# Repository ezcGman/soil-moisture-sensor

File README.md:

# Soil Moisture Sensor
This is one of my first self designed PCBs in KiCad. It's a simple circuit which makes use of an ESP8266 and a soil moisture sensor to observe your plants. The cool thing: My custom socket supports the ESP-12E/F, the ESP-8 and the cool ESP-7, which comes with an external antennna!

## Credits
Shoutout to Quindor from QuinLED.info, the LED master himself. He tought me a lot about KiCad, PCB design and some more electrical engineering fundamentals! While I'm still miles away from being perfect, with his help I really feel confident in what I'm doing here!

## KiCad dependencies
It might happen that KiCad is missing my custom footprints. You can find and download them here and then add them to KiCad: https://github.com/ezcGman/andys-footprints

## Parts list
All these parts can be easily found on AliExpress (except the PCBs ;) ):

- 1x The PCB in this folder, printed e.g. at PCBWay
- 1x 3.2V LiFePO4 battery in AA form factor
- 1x AA battery holder for THT mounting
- 1x capactive soil moisture sensor (some notes on capacitive vs. resistive sensors can be found a bit further down)
- 1x bare ESP8266 module, so no devboard like the famous NodeMCU or D1 Mini. The socket supports the ESP-12E/F, ESP-8 and ESP-7. But in the end, there are only two choices:
  - ESP-12E/F: If you don't need an external antenna / your Wi-Fi signal is good, get this one. It's super common, easy to get and cheap.
  - ESP-7: If you do need an external antenna, get this one. Often also comes directly with an antenna! 
- 1x NPN transistor. Probably most transistors are fine, but I suggest the 2n2222(a) which is super common and totally sufficient for this
- 1x 0805 SMD capacitor of 10µF or bigger. But 0805 SMD caps are usually limited to ~40µF. So whatever u have around
- 1x 0805 SMD capacitor of 100nF
- 1x 0805 resistor of 1kΩ
- 2x 0805 resistor of 10kΩ
- 1x 0805 resistor of 100kΩ
- 1x 0805 resistor of 220kΩ
- 2x **2mm** (**not** 2.54mm!!) single row pin headers of 8 pins each
- 1x 2.54mm single row pin header of 3 pins

## Tools list
### Required
- A soldering iron
- Soldering tin

### Optional
- For SMD components:
  - A hot air soldering/reflow station. However, those are 0805 SMD components which can be done with a soldering iron
  - Solder paste
  - Tweezers

## The code
If you're familiar with ESP coding, this should all be straight forward, but some key things in there:
* The whole code is in setup() as the ESP goes through it when doing timed deep sleep using the GPIO16-to-RST method. Because the "wake up" is actually a reset, because the RST is pulled low.
* I'm using the sensor in Home Assistant through MQTT, so the code has some MQTT logic
* Both my Wi-Fi and MQTT connect routines have some reconnect logic.
* GPIO4 is used to switch on the sensor, so this is one of the very first things the code does. This is done by pulling it HIGH, which will switch the transistor which then makes the full circuit of the sensor complete, by letting the electrones flow from GND to the sensor.
* I then just read from the A0 pin, convert it in C-super-complicated-style (Python developer speaking here!) to a char and dropping it into an MQTT topic.
* It also has some percentage calculation, which is based on my own measurements of the sensor. These are the "air value" (so sensor just laying around) and the "water value" (which is the sensor put into a glas of clear water).
* Another thing is a "dry/wet threshold", which is based on my girlfriend: She said "Andy, this is now dry!". And I took this as the threshold (minus a little bit for earlier alerts) for considering a plant being dry. Note, that this may vary by plant and flower soil used.
* Ultimately not needed, but for easier checking if the battery is empty (=no signal is sent anymore): A "last updated" timestamp also dropped into the MQTT topic

### Dependencies
* Arduino Client for MQTT, >=v2.8.0: https://pubsubclient.knolleary.net/
* Optional (can use built-in DateTime): ESPDateTime, >=v1.0.4: https://github.com/mcxiaoke/ESPDateTime

## Schematic

## Why a bare ESP-12F, why not using a devboard like D1 or NodeMCU?
Easy answer: Power consumption + deep sleep. All these dev boards have an USB UART that is **always on**, even in deep sleep. And this eats a lot of energy. There is a really good post about why you should use ESP-12F over these devboards: https://github.com/z2amiller/sensorboard/blob/master/PowerSaving.md
Also: There is a reason why they are called **dev**boards ;) They are not really meant to be used "in production."

## Which kind of soil moisture sensors exist / should I use?
### 1. Electrical conduction sensors (Don't use: Boooo!)
When I was first playing with these soil moisture sensors, I've started with these sensors, which have a (visible) copper/some metal layer and two legs: They measure the soil moisture based on the electrical conduction of the soil / between the two legs.
The downside of these is that they can corrode and actually harm the plants, instead of surveiling them ;) And I don't know what upsides they actually have compared to:

### 2. Capacitive Soil Moisture Sensor (Use: Coooool!)
You guessed it: These sensors work by measuring the capacitance of the sensor (or it's layers (the electrodes)), where the soil and water function as the dielectric. These do not have copper layers being exposed which could corrode, so make them safe to use in any plant.
If you **really** want to deep dive into how these sensors work and how to properly calibrate them, lead this publication: https://www.researchgate.net/publication/342751186_Capacitive_Soil_Moisture_Sensor_Theory_Calibration_and_Testing

## How it looks

## Example application with an ESP-07 / external antenna outside (waterproof)
*Yes, I know: This is currently an ESP-12F, because I'm waiting for the ESP-07 to arrive. But then this will be powered by an ESP-07 ;)*
I just used an old jelly glass, drilled two holes in it and sealed them with hot glue. Therefore it's perfectly waterproof :)

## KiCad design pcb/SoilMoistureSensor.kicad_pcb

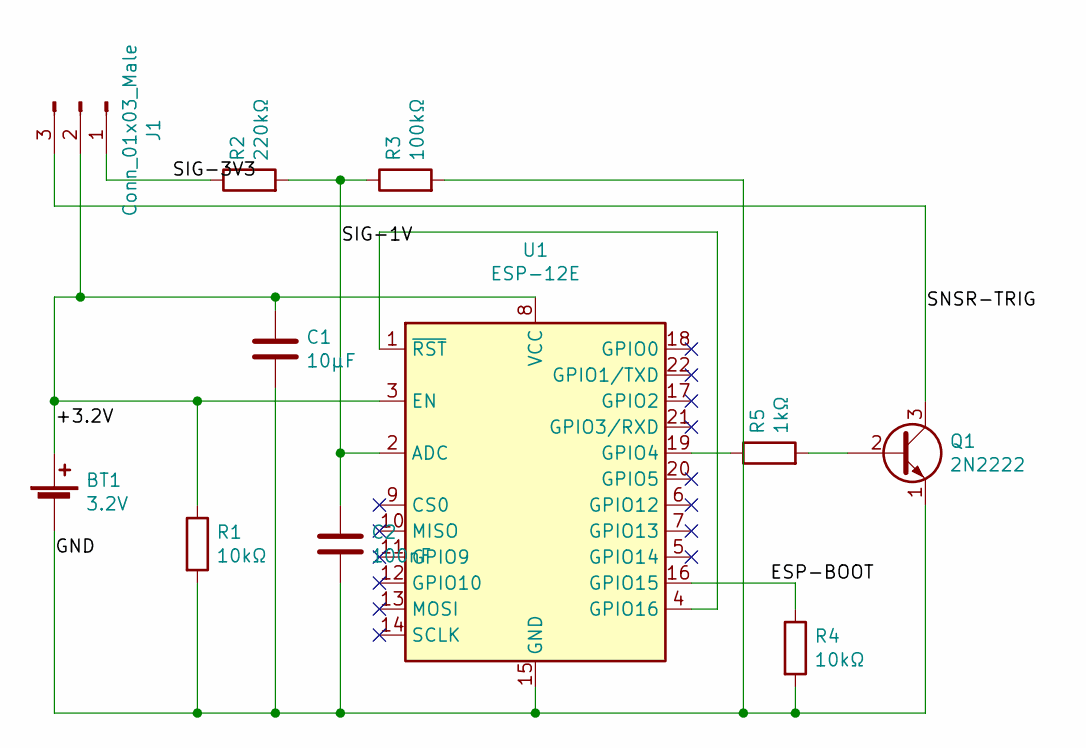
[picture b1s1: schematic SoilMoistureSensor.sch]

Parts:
BT1: 3.2V; BatteryHolder_Keystone_2460_1xAA-removed-holes
C1: 10µF; C_0805_2012Metric_Pad1.18x1.45mm_HandSolder
C2: 100nF; C_0805_2012Metric_Pad1.18x1.45mm_HandSolder
J1: Conn_01x03_Male; PinHeader_1x03_P2.54mm_Vertical-Fixed-SilkScreen
Q1: 2N2222; TO-92_HandSolder
R1, R4: 10kΩ; R_0805_2012Metric_Pad1.20x1.40mm_HandSolder
R2: 220kΩ; R_0805_2012Metric_Pad1.20x1.40mm_HandSolder
R3: 100kΩ; R_0805_2012Metric_Pad1.20x1.40mm_HandSolder
R5: 1kΩ; R_0805_2012Metric_Pad1.20x1.40mm_HandSolder
U1: ESP-12E; ESP-12-Socket

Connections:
/+3.2V: BT1.1 (+), C1.1, J1.2, R1.1, U1.3 (EN), U1.8 (VCC)
/ESP-BOOT: R4.1, U1.16 (GPIO15)
/GND: BT1.2 (-), C1.2, C2.2, Q1.1 (E), R1.2, R3.2, R4.2, U1.15 (GND)
/SIG-1V: C2.1, R2.2, R3.1, U1.2 (ADC)
/SIG-3V3: J1.1, R2.1
/SNSR-TRIG: J1.3, Q1.3 (C)
unnamed: Q1.2 (B), R5.2
unnamed: R5.1, U1.19 (GPIO4)
unnamed: U1.1 (~RST), U1.4 (GPIO16)

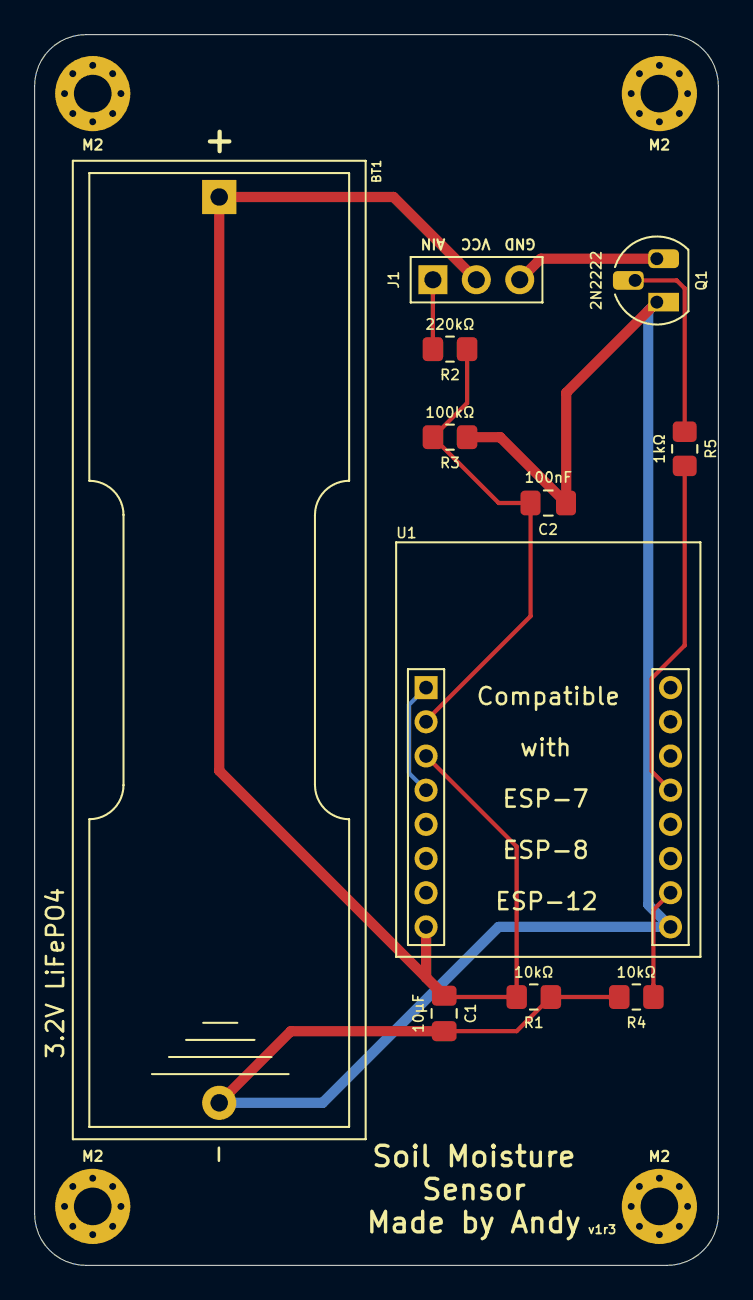
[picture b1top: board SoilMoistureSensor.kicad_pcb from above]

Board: 2 copper layers, 40.0 x 72.0 mm, 15 parts (0 on the bottom side), 9 nets.

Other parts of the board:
M2, M2#2, M2#3, M2#4: MountingHole_2.2mm_M2_Pad_Via

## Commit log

2021-06-08 Fixed GPIO
2021-06-08 Added schematic
2021-06-10 Fixed turning off LED
2021-06-14 Some Wi-Fi improvements
2021-06-14 PCB v1r3: Made it 40mm width again, as it fits perfectly in old tomato sauce glasses ;)
